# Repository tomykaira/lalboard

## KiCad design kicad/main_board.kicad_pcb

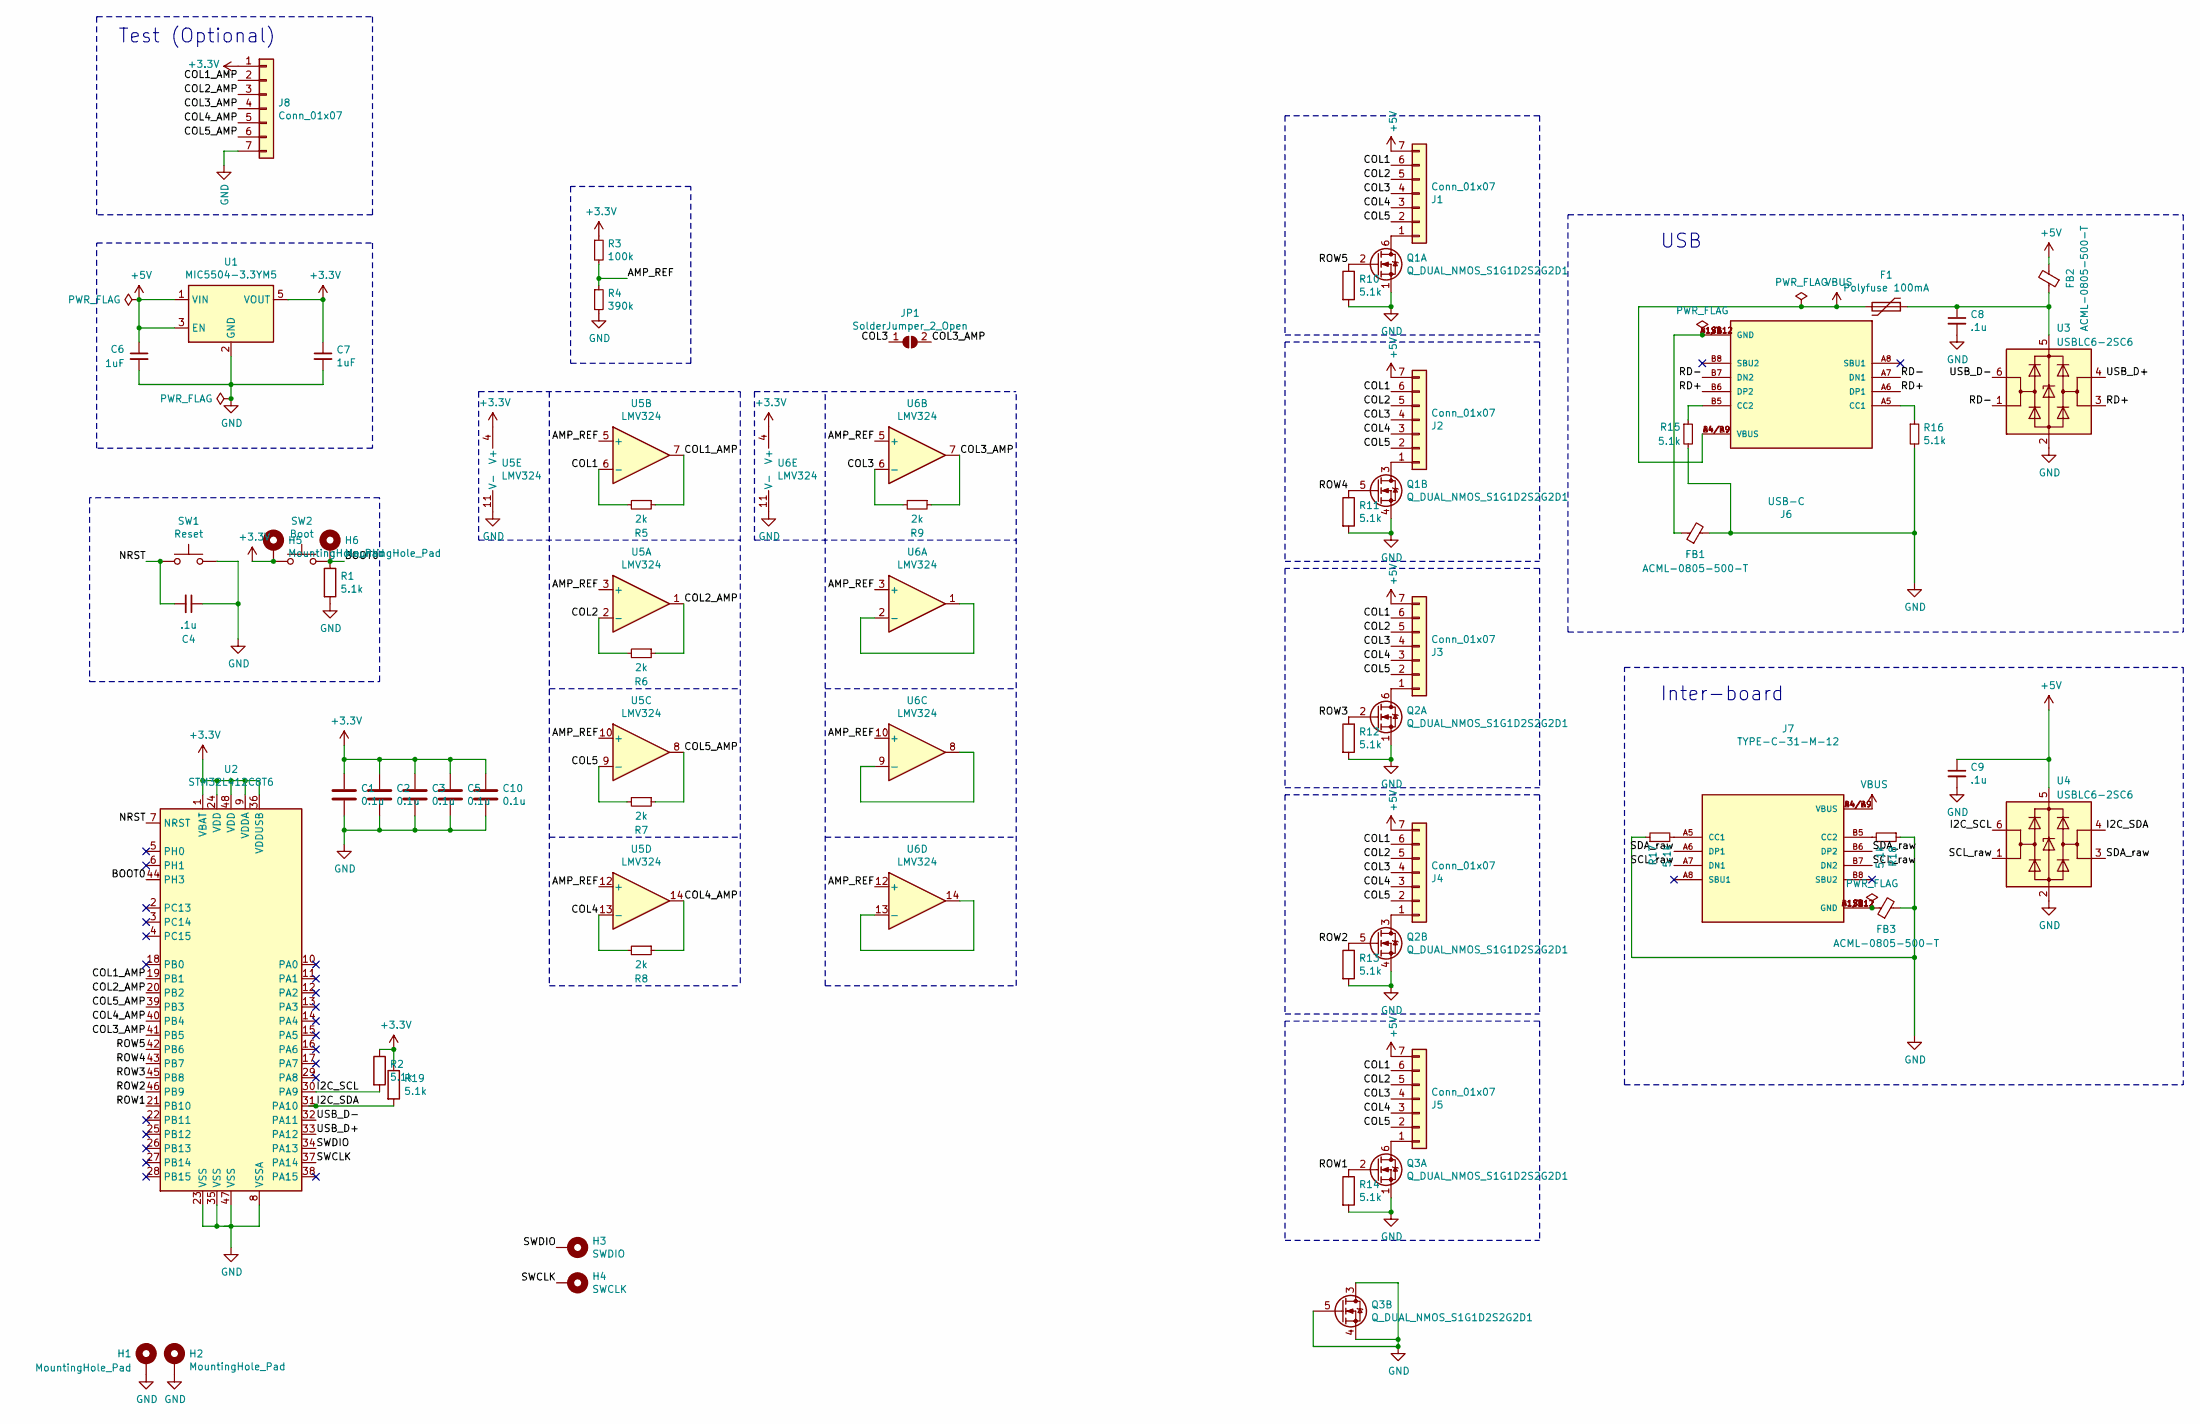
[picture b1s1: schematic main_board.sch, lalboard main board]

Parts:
C1, C2, C3, C5, C10: 0.1u; C_0805_2012Metric_Pad1.15x1.40mm_HandSolder
C4: .1u; C_0805_2012Metric_Pad1.15x1.40mm_HandSolder; Voltage 16V; Tolerance 10%
C6, C7: 1uF; C_0805_2012Metric_Pad1.15x1.40mm_HandSolder
C8, C9: .1u; C_0805_2012Metric_Pad1.15x1.40mm_HandSolder
F1: Polyfuse 100mA; Fuse_1210_3225Metric_Pad1.42x2.65mm_HandSolder
FB1, FB2, FB3: ACML-0805-500-T; L_0805_2012Metric_Pad1.15x1.40mm_HandSolder
H1, H2: MountingHole_Pad; MountingHole_3.2mm_M3_DIN965_Pad
H3: SWDIO; TestPoint_THTPad_D2.0mm_Drill1.0mm
H4: SWCLK; TestPoint_THTPad_D2.0mm_Drill1.0mm
H5, H6: MountingHole_Pad; TestPoint_THTPad_D2.0mm_Drill1.0mm
J1, J2, J3, J4, J5, J8: Conn_01x07; JST_ZH_B7B-ZR_1x07_P1.50mm_Vertical
J6: USB-C; GCT_USB4110-GF-A_REVB
J7: TYPE-C-31-M-12; GCT_USB4110-GF-A_REVB
JP1: SolderJumper_2_Open; SolderJumper-2_P1.3mm_Open_RoundedPad1.0x1.5mm
Q1, Q2, Q3: Q_DUAL_NMOS_S1G1D2S2G2D1; SOT-363_SC-70-6_Handsoldering
R1, R2, R10, R11, R12, R13, R14, R15, R16, R17, R18, R19: 5.1k; R_0805_2012Metric_Pad1.15x1.40mm_HandSolder
R3: 100k; R_0805_2012Metric_Pad1.15x1.40mm_HandSolder
R4: 390k; R_0805_2012Metric_Pad1.15x1.40mm_HandSolder
R5, R6, R7, R8, R9: 2k; R_0805_2012Metric_Pad1.15x1.40mm_HandSolder
SW1: Reset; SW_SPST_B3U-1000P; Part 1825910-6
SW2: Boot; SW_SPST_B3U-1000P; Part 1825910-6
U1: MIC5504-3.3YM5; SOT-23-5
U2: STM32L412C8T6; TQFP-48_7x7mm_P0.5mm
U3, U4: USBLC6-2SC6; SOT-23-6
U5, U6: LMV324; TSSOP-14_4.4x5mm_P0.65mm

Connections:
+3V3: C1.1, C2.1, C3.1, C5.1, C7.1, C10.1, H5.1, J8.1, R2.1, R3.1, R19.1, SW2.2, U1.5 (VOUT), U2.1 (VBAT), U2.9 (VDDA), U2.24 (VDD), U2.36 (VDDUSB), U2.48 (VDD), U5.4 (V+), U6.4 (V+)
+5V: C6.1, C9.1, FB2.2, J1.7, J2.7, J3.7, J4.7, J5.7, U1.1 (VIN), U1.3 (EN), U4.5 (VBUS)
/AMP_REF: R3.2, R4.1, U5.3 (+), U5.5 (+), U5.10 (+), U5.12 (+), U6.3 (+), U6.5 (+), U6.10 (+), U6.12 (+)
/BOOT0: H6.1, R1.1, SW2.1, U2.44 (PH3)
/COL1: J1.6, J2.6, J3.6, J4.6, J5.6, R5.2, U5.6 (-)
/COL1_AMP: J8.2, R5.1, U2.19 (PB1), U5.7
/COL2: J1.5, J2.5, J3.5, J4.5, J5.5, R6.2, U5.2 (-)
/COL2_AMP: J8.3, R6.1, U2.20 (PB2), U5.1
/COL3: J1.4, J2.4, J3.4, J4.4, J5.4, JP1.1 (A), R9.2, U6.6 (-)
/COL3_AMP: J8.4, JP1.2 (B), R9.1, U2.41 (PB5), U6.7
/COL4: J1.3, J2.3, J3.3, J4.3, J5.3, R8.2, U5.13 (-)
/COL4_AMP: J8.5, R8.1, U2.40 (PB4), U5.14
/COL5: J1.2, J2.2, J3.2, J4.2, J5.2, R7.2, U5.9 (-)
/COL5_AMP: J8.6, R7.1, U2.39 (PB3), U5.8
/I2C_SCL: R2.2, U2.30 (PA9), U4.6 (I/O1)
/I2C_SDA: R19.2, U2.31 (PA10), U4.4 (I/O2)
/NRST: C4.2, SW1.1, U2.7 (NRST)
/RD+: J6.A6 (DP1), J6.B6 (DP2), U3.3 (I/O2)
/RD-: J6.A7 (DN1), J6.B7 (DN2), U3.1 (I/O1)
/ROW1: Q3.2 (G), R14.1, U2.21 (PB10)
/ROW2: Q2.5 (G), R13.1, U2.46 (PB9)
/ROW3: Q2.2 (G), R12.1, U2.45 (PB8)
/ROW4: Q1.5 (G), R11.1, U2.43 (PB7)
/ROW5: Q1.2 (G), R10.1, U2.42 (PB6)
/SCL_raw: J7.A7 (DN1), J7.B7 (DN2), U4.1 (I/O1)
/SDA_raw: J7.A6 (DP1), J7.B6 (DP2), U4.3 (I/O2)
/SWCLK: H4.1, U2.37 (PA14)
/SWDIO: H3.1, U2.34 (PA13)
/USB_D+: U2.33 (PA12), U3.4 (I/O2)
/USB_D-: U2.32 (PA11), U3.6 (I/O1)
GND: C1.2, C2.2, C3.2, C4.1, C5.2, C6.2, C7.2, C8.2, C9.2, C10.2, FB1.2, FB3.2, H1.1, H2.1, J8.7, Q1.1 (S), Q1.4 (S), Q2.1 (S), Q2.4 (S), Q3.1 (S), Q3.3 (D), Q3.4 (S), Q3.5 (G), R1.2, R4.2, R10.2, R11.2, R12.2, R13.2, R14.2, R15.2, R16.2, R17.1, R18.1, SW1.2, U1.2 (GND), U2.8 (VSSA), U2.23 (VSS), U2.35 (VSS), U2.47 (VSS), U3.2 (GND), U4.2 (GND), U5.11 (V-), U6.11 (V-)
unnamed: C8.1, F1.1, FB2.1, U3.5 (VBUS)
unnamed: FB1.1, J6.A1/B12 (GND), J6.B1/A12 (GND), J6.S1 (GND), J6.S2 (GND), J6.S3 (GND), J6.S4 (GND)
unnamed: FB3.1, J7.A1/B12 (GND), J7.B1/A12 (GND), J7.S1 (GND), J7.S2 (GND), J7.S3 (GND), J7.S4 (GND)
unnamed: J1.1, Q1.6 (D)
unnamed: J2.1, Q1.3 (D)
unnamed: J3.1, Q2.6 (D)
unnamed: J4.1, Q2.3 (D)
unnamed: J5.1, Q3.6 (D)
unnamed: J6.A5 (CC1), R16.1
unnamed: J6.B5 (CC2), R15.1
unnamed: J7.A5 (CC1), R17.2
unnamed: J7.B5 (CC2), R18.2
unnamed: U6.1, U6.2 (-)
unnamed: U6.8, U6.9 (-)
unnamed: U6.13 (-), U6.14
VBUS: F1.2, J6.A4/B9 (VBUS), J6.B4/A9 (VBUS), J7.A4/B9 (VBUS), J7.B4/A9 (VBUS)

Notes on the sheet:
USB
Inter-board
Test (Optional)

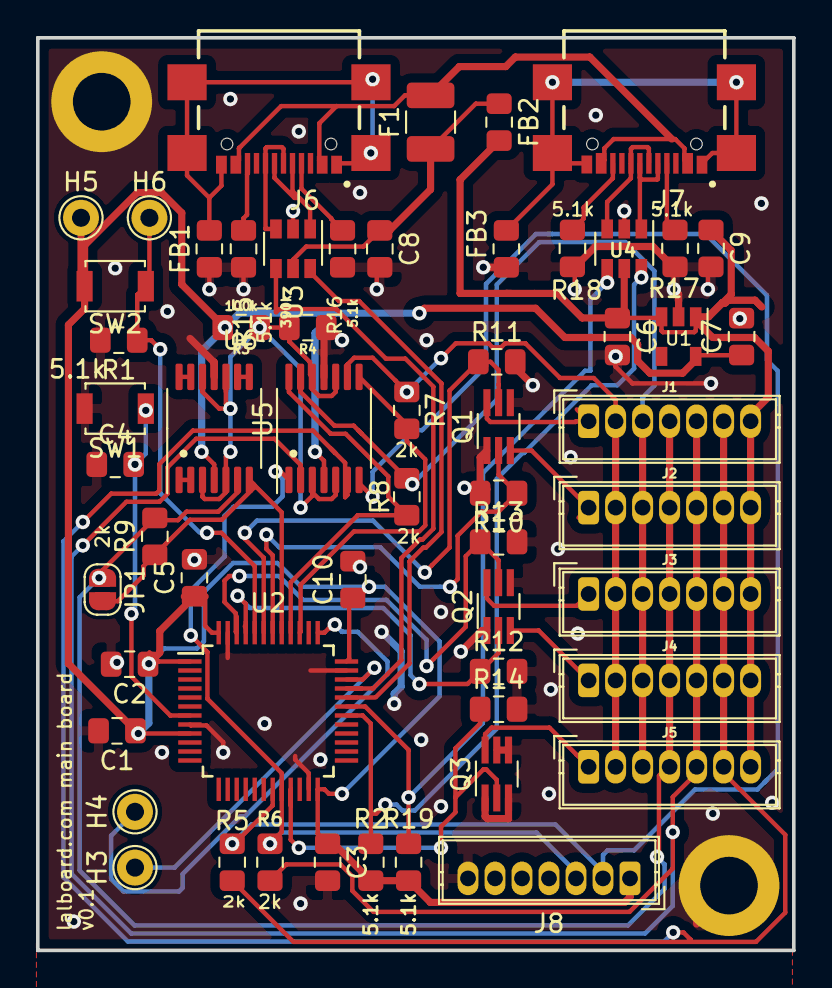
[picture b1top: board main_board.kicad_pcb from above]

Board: 2 copper layers, 42.0 x 50.7 mm, 59 parts (0 on the bottom side), 47 nets.

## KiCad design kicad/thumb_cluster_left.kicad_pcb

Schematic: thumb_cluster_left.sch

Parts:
H1, H2: MountingHole_Pad; MountingHole_3.2mm_M3_Pad
IR1, IR2, IR4, IR5: IR908-7C-F
J1: Conn_01x07; JST_ZH_B7B-ZR_1x07_P1.50mm_Vertical
JP1, JP2, JP3, JP4, JP9, JP10, JP17, JP18, JP19, JP20: SolderJumper_3_Open; SolderJumper-3_P1.3mm_Open_Pad1.0x1.5mm_NumberLabels
PT1, PT2, PT4, PT5: PT908-7B-F; PT908-7C-F
R1: 56; R_1206_3216Metric_Pad1.42x1.75mm_HandSolder
R2: 100; R_1206_3216Metric_Pad1.42x1.75mm_HandSolder
R3: 5.1k; R_1206_3216Metric_Pad1.42x1.75mm_HandSolder
R4: 180; R_1206_3216Metric_Pad1.42x1.75mm_HandSolder
R5: 150; R_1206_3216Metric_Pad1.42x1.75mm_HandSolder
SW1: D2FS-F-N; Omron-D2FS-F-N-MFG; voltage rating DC 6V; mouser part number 653-D2FS-F-N; digikey description SWITCH SNAP ACT SPST-NO 100MA 6V
SW2: SW_Push; CMI625501D06

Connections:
+5V: J1.1, JP1.1, JP2.1, JP3.3, JP4.3, JP9.3, JP10.3, JP17.3, JP18.3, JP19.3, JP20.3, R3.2
/5VGND: IR1.2, IR2.2, IR4.2, IR5.2, JP1.2
/GND5V: JP2.2, R1.1, R2.1, R4.1, R5.1
C1: J1.2, JP3.1, JP4.1
C2: J1.3, JP9.1, JP10.1
C3: J1.4, R3.1, SW1.1, SW2.1
C4: J1.5, JP17.1, JP18.1
C5: J1.6, JP19.1, JP20.1
GND: H1.1, H2.1, J1.7, JP1.3, JP2.3, SW1.2, SW2.2
unnamed: IR1.1, R1.2
unnamed: IR2.1, R2.2
unnamed: IR4.1, R4.2
unnamed: IR5.1, R5.2
unnamed: JP3.2, PT1.2
unnamed: JP4.2, PT1.1
unnamed: JP9.2, PT2.2
unnamed: JP10.2, PT2.1
unnamed: JP17.2, PT4.2
unnamed: JP18.2, PT4.1
unnamed: JP19.2, PT5.2
unnamed: JP20.2, PT5.1

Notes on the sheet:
Upper Outer
Lower Outer
Down
Inner
Mode

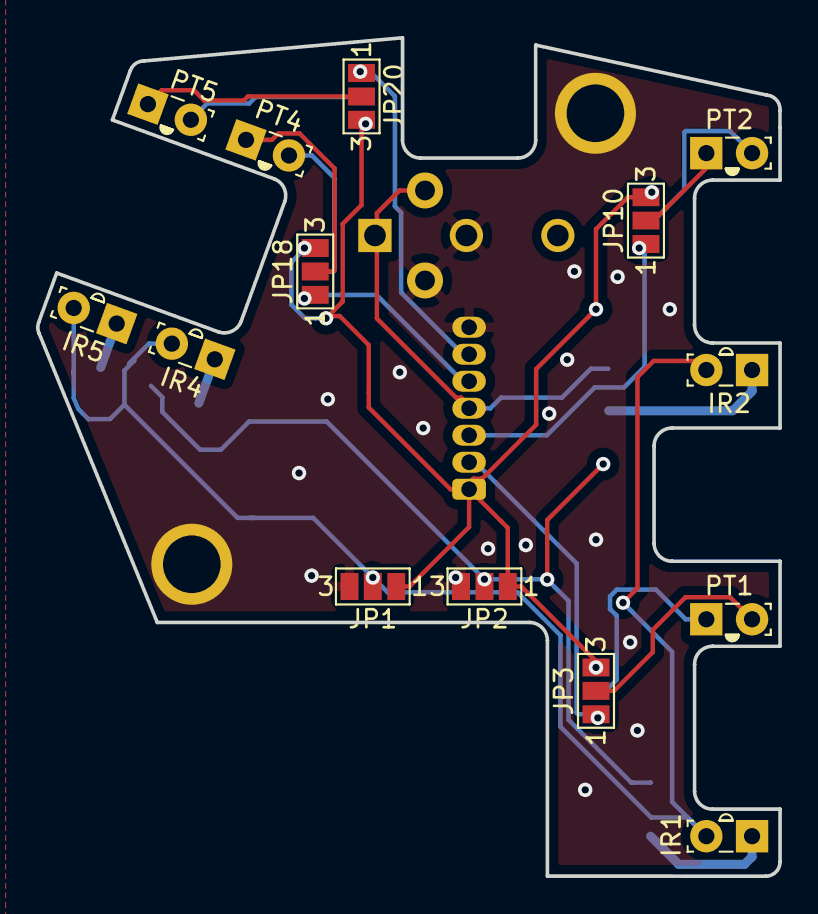
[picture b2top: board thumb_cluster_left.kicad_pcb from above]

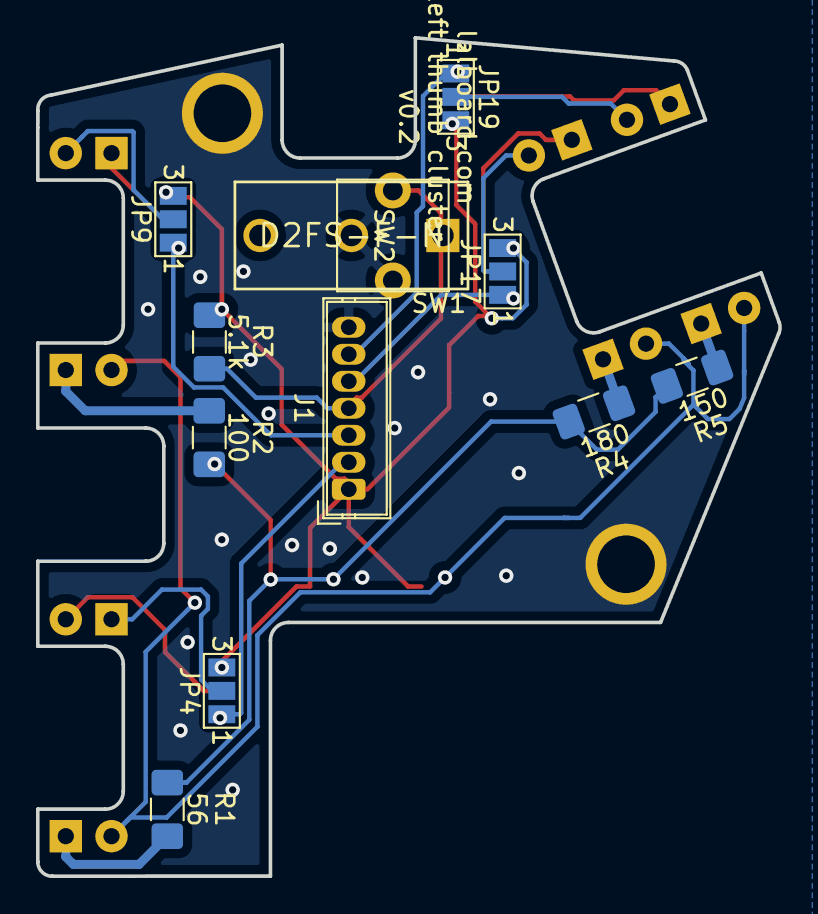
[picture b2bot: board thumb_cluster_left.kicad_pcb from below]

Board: 2 copper layers, 41.2 x 46.6 mm, 28 parts (12 on the bottom side), 21 nets.

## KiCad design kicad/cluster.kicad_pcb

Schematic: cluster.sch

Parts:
IR1, IR2, IR4, IR5: OP140C; IR908-7C-F
J1: Conn_01x07; JST_ZH_S7B-ZR_1x07_P1.50mm_Horizontal
PT1, PT2, PT4, PT5: OP550A; PT908-7C-F
R1, R2, R4, R5: 150; R_1206_3216Metric_Pad1.42x1.75mm_HandSolder
R3: 5.1k; R_0805_2012Metric_Pad1.15x1.40mm_HandSolder
SW1: SW_Push; SW_CHOC

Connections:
+5V: IR1.2, IR2.2, IR4.2, IR5.2, J1.1, PT1.2, PT2.2, PT4.2, PT5.2, R3.2
C1: J1.2, PT1.1
C2: J1.3, PT2.1
C3: J1.4, R3.1, SW1.1
C4: J1.5, PT4.1
C5: J1.6, PT5.1
GND: J1.7, R1.1, R2.1, R4.1, R5.1, SW1.2
unnamed: IR1.1, R1.2
unnamed: IR2.1, R2.2
unnamed: IR4.1, R4.2
unnamed: IR5.1, R5.2

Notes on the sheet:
Down
West
South
North

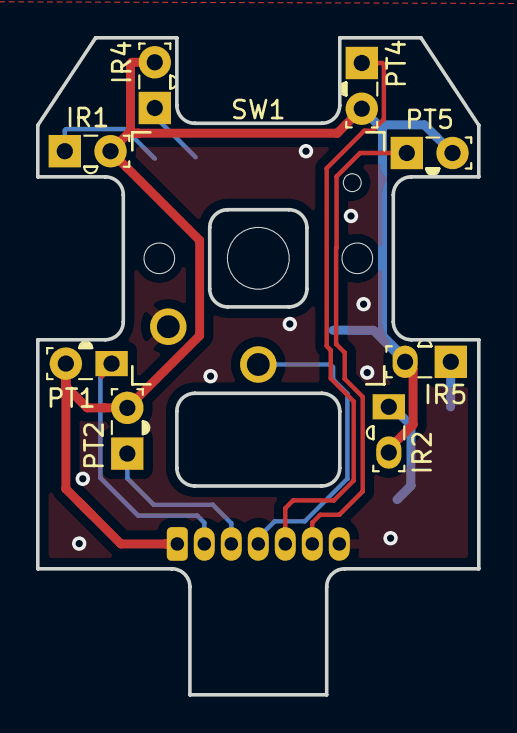
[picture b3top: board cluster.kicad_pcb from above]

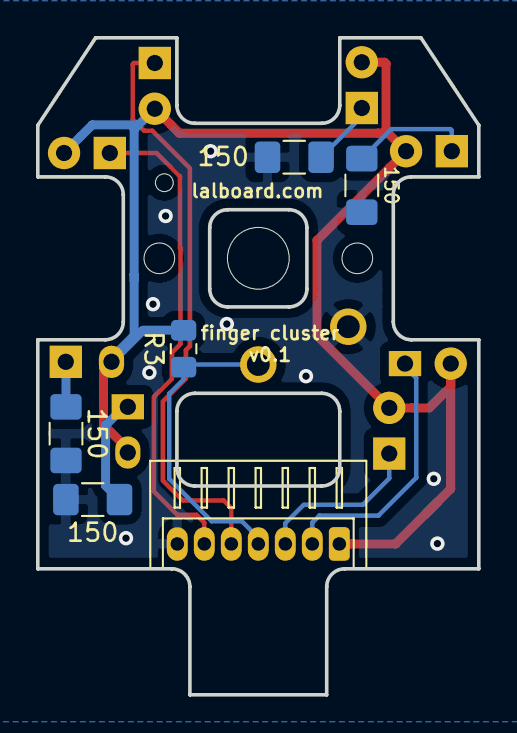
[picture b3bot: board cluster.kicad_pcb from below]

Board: 2 copper layers, 24.5 x 36.5 mm, 15 parts (6 on the bottom side), 11 nets.

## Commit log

2021-08-15 wip: update mainboard with STM32
2021-08-16 Change mid switch to choc
2021-08-16 Edit cluster board for choc key switch
2021-08-16 Adjust push angle for less precise 3D printer
2021-08-18 Update kicad pcb data to change parts
2022-01-30 Customize
